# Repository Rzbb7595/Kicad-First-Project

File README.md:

# Kicad-First-Project
this is redo of first kicad project. I am doing it again cause I've changed footprints in the previous one.

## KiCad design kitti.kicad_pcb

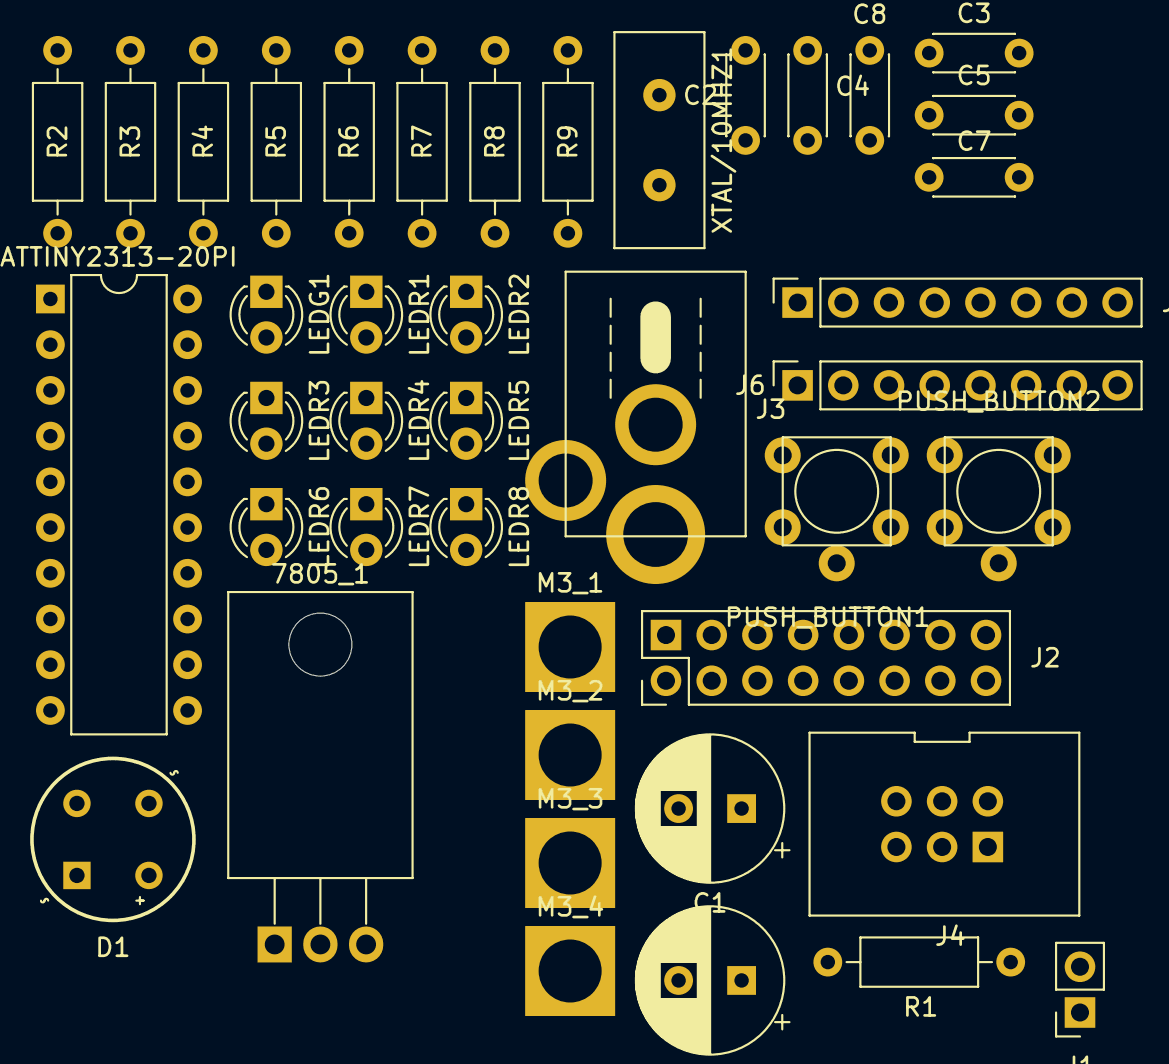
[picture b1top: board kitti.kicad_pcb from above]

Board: 2 copper layers, 42 parts (0 on the bottom side), 40 nets, no tracks yet.

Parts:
7805_1: 7805_TO220_1.5A; TO-220
ATTINY2313-20PI: ATTINY2313-20PI_DIL20; DIL20
C1, C6: 100UF_50V_ELE; C_P_3_5_8
C2, C4, C7, C8: 100NF_50V_CER; C5_0
C3, C5: 27PF_200V_CER; C5_0
D1: 2W10M
J1: SOCKET_1X2; SOCKET_1x2
J2: ROW_VERT_2X8; ROW_VERT_2x8
J3: DC_CON_2_1MM_MALE; DCR21P
J4: ROW_VERT_2X3; AVR_ISP
J5, J6: SOCKET_1X8; SOCKET_1x8
LEDG1: GreenLED; LED
LEDR1, LEDR2, LEDR3, LEDR4, LEDR5, LEDR6, LEDR7, LEDR8: RedLED; LED
M3_1, M3_2, M3_3, M3_4: M3
PUSH_BUTTON1, PUSH_BUTTON2: PUSH_BUTTON; SKHHQV
R1: 330R; R3_5W
R2, R3, R4, R5, R6, R7, R8, R9: 680R; R3_5W
XTAL/10MHZ1: XTAL_10MHZ; XTAL

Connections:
+5V: 7805_1.3 (VO), ATTINY2313-20PI.20 (VCC), C4.2, C6.1, C7.2, C8.2, J1.1, J4.1, LEDR1.2 (A), LEDR2.2 (A), LEDR3.2 (A), LEDR4.2 (A), LEDR5.2 (A), LEDR6.2 (A), LEDR7.2 (A), LEDR8.2 (A), R1.2
GNDD: 7805_1.2 (GND), ATTINY2313-20PI.10 (GND), C1.2, C2.1, C3.1, C4.1, C5.1, C6.2, C7.1, C8.1, D1.3 (-), J1.2, J4.5, J6.8, LEDG1.1 (K), PUSH_BUTTON1.1, PUSH_BUTTON1.4 (2), PUSH_BUTTON1.5 (GND), PUSH_BUTTON2.1, PUSH_BUTTON2.4 (2), PUSH_BUTTON2.5 (GND)
unnamed: ATTINY2313-20PI.1 (PA2/~RESET), J4.6
unnamed: ATTINY2313-20PI.2 (PD0), J6.1
unnamed: ATTINY2313-20PI.3 (PD1), J6.2
unnamed: ATTINY2313-20PI.4 (PA1/XTAL2), C3.2, XTAL/10MHZ1.1
unnamed: ATTINY2313-20PI.5 (PA0/XTAL1), C5.2, XTAL/10MHZ1.2
unnamed: ATTINY2313-20PI.6 (PD2), J6.3, PUSH_BUTTON1.2 (A), PUSH_BUTTON1.3 (K)
unnamed: ATTINY2313-20PI.7 (PD3), J6.4, PUSH_BUTTON2.2 (A), PUSH_BUTTON2.3 (K)
unnamed: ATTINY2313-20PI.8 (PD4), J6.5
unnamed: ATTINY2313-20PI.9 (PD5), J6.6
unnamed: ATTINY2313-20PI.11 (PD6), J6.7
unnamed: ATTINY2313-20PI.12 (PB0), J2.1, J5.1
unnamed: ATTINY2313-20PI.13 (PB1), J2.3, J5.2
unnamed: ATTINY2313-20PI.14 (PB2), J2.5, J5.3
unnamed: ATTINY2313-20PI.15 (PB3), J2.7, J5.4
unnamed: ATTINY2313-20PI.16 (PB4), J2.9, J5.5
unnamed: ATTINY2313-20PI.17 (PB5), J2.11, J4.3, J5.6
unnamed: ATTINY2313-20PI.18 (PB6), J2.13, J4.2, J5.7
unnamed: ATTINY2313-20PI.19 (PB7), J2.15, J4.4, J5.8
unnamed: D1.1, J3.2
unnamed: D1.2, J3.1, J3.3
unnamed: 7805_1.1 (VI), C1.1, C2.2, D1.4 (+)
unnamed: LEDG1.2 (A), R1.1
unnamed: LEDR1.1 (K), R2.1
unnamed: J2.2, R2.2
unnamed: LEDR2.1 (K), R3.1
unnamed: J2.4, R3.2
unnamed: LEDR3.1 (K), R4.1
unnamed: J2.6, R4.2
unnamed: LEDR4.1 (K), R5.1
unnamed: J2.8, R5.2
unnamed: LEDR5.1 (K), R6.1
unnamed: J2.10, R6.2
unnamed: LEDR6.1 (K), R7.1
unnamed: J2.12, R7.2
unnamed: LEDR7.1 (K), R8.1
unnamed: J2.14, R8.2
unnamed: LEDR8.1 (K), R9.1
unnamed: J2.16, R9.2
